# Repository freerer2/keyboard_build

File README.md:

## Note
빌드 한 키보드의 부품 정보 모음.
내 손길이 조금이라도 닿은 경우에만 목록에 추가됨.

## Keyboard List
- [blackpill_chayribdis_nano](/blackpill_chayribdis_nano/) : chayribdis_nano 블랙필버전(케이스 수정)
- [cantor-remix_MX](https://github.com/freerer2/cantor-remix_MX) : cantor-remix MX버전(PCB수정)
- [lazyboy36](/lazyboy36/) : 36키 모노블럭 키보드(ergogen 사용)

## unused
- ~~[wireless_charybdis_nano](/wireless_charybdis_nano/) : chayribdis_nano 무선버전(작성중)~~

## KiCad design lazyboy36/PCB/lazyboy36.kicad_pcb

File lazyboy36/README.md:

# LAZYBOY36
<center></center>
<center></center>

스플릿 키보드는 휴대시 trrs 케이블, USB 케이블, 오른쪽 키보드, 왼쪽 키보드  
아주 주렁주렁 정신이 없습니다.

이제는 USB 케이블과 키보드 한개만 챙기세요. Lazyboy36 입니다.

## Features

1. 당신의 손가락 건강을 위한 컬럼스태거 구조
2. 당신의 손목 건강을 위한 36키
3. 당신의 어깨 건강을 위한 20도 각도의 스플릿 구조
4. 당신의 타건감 취향을 위한 핫스왑 지원
5. 빌드의 범용성을 위한 Pro Micro 모양의 MCU 지원
6. 배터리 걱정할 필요없는 ONLY 유선키보드
7. 그 유명한 Miryoku 배열의 키맵을 한국인의 손에 맞춘 개조판 펌웨어 기본 지원
   - [lazybones](https://github.com/freerer2/qmk_firmware/tree/master/users/lazybones)
8. ~~휴대성이 좋은 아주 얇은 키보드~~(증명필요)
   - ~~키캡 없이 범폰 포함 총 높이 : 약 14mm~~
   - ~~케이스 높이 : 5.2mm~~

## Quick Links

- Ergogen Config: [config.yaml](config.yaml)
  - Ergogen command
  ```bash
  ergogen . && for i in output/cases/*.jscad; do npx @jscad/cli@1 "$i" -of stla; done
  ```
- PCB Design: [output/pcbs/lazyboy36.kicad_pcb](output/pcbs/lazyboy36.kicad_pcb)
- 3D Printable case: [output/cases/case.stl](output/cases/case.stl)
- QMK Config: [qmk_config/](qmk_config/)

## Bill of Materials (BOM)

### Keyboard

| Part name                         | Amount | Link                                                                   | note          |
| :-------------------------------- | -----: | :--------------------------------------------------------------------- | :------------ |
| PCB                               |      1 | [/lazyboy36/output/pcbs/gerber.zip](/lazyboy36/output/pcbs/gerber.zip) | JLC 주문완료  |
| MCU(such as the Pro Micro)        |      1 |                                                                        | 알리 주문완료 |
| Pin headers(optional)             |     24 |                                                                        | 알리 주문완료 |
| OLED(optional)                    |      1 |                                                                        |
| Choc v1 switchs(PG1350)           |     36 | https://ko.aliexpress.com/item/1005005883472162.html                   | 알리 주문완료 |
| Choc v1 keycaps                   |     36 | https://github.com/freerer2/choc_keycaps                               | JLC 주문완료  |
| 1N4148 SOD123 or DO-35            |     36 | https://ko.aliexpress.com/item/1005002882901030.html                   | 있음          |
| Kailh low profile hot-swap socket |     36 | https://ko.aliexpress.com/item/1005006345544915.html                   | 알리 주문완료 |
| Button, 4x4x1.5                   |      1 | https://ko.aliexpress.com/item/1005003918757433.html                   | 있음          |

### Case

| Part name                     | Amount | Link                                                                 | note          |
| :---------------------------- | -----: | :------------------------------------------------------------------- | :------------ |
| Case                          |      1 | [/lazyboy36/output/cases/case.stl](/lazyboy36/output/cases/case.stl) | JLC 주문완료  |
| Black 10x2mm bumpon           |      8 | https://ko.aliexpress.com/item/1005005287385986.html                 | 있음          |
| Screws, M2 3mm                |      8 | https://smartstore.naver.com/boltmall/products/106695149             | 알리 주문완료 |
| Heated screw insert, M2x2x3.2 |      8 | https://ko.aliexpress.com/item/1005004870993068.html                 | 알리 주문완료 |

# TODO-LIST

## ERGOGEN

- [x] 키보드 정의

## PCB

- [x] 라우팅

## FIRMWARE

- [x] QMK
- [ ] ~~VIA~~(고민중)

## BUILD

- [x] 재료준비
  - [x] PCB
    - [x] MCU : RP2040 PROMICRO
    - [x] SWITCH : PG1350
    - [x] KEYCAPS : MBK
    - [x] DIODE : SOD123
    - [x] HEADER PIN FEMALE : 315-43-112-41-003000
    - [x] HEADER PIN MALE : 3320-0-00-15-00-00-03-0
    - [x] HOTSWAP SOCKET
    - [x] RST BUTTON
  - [ ] CASE
    - [x] INSERT
    - [x] SCREWS
    - [x] BUMPON

## ETC

- [ ] README 작성
  - [x] Introduction
  - [x] Features
  - [x] Quick Links
    - [x] ergogen config yaml
    - [x] PCB
    - [x] CASE
    - [x] Firmware
      - [x] QMK
      - [ ] ~~VIA~~(고민중)
  - [x] BOM

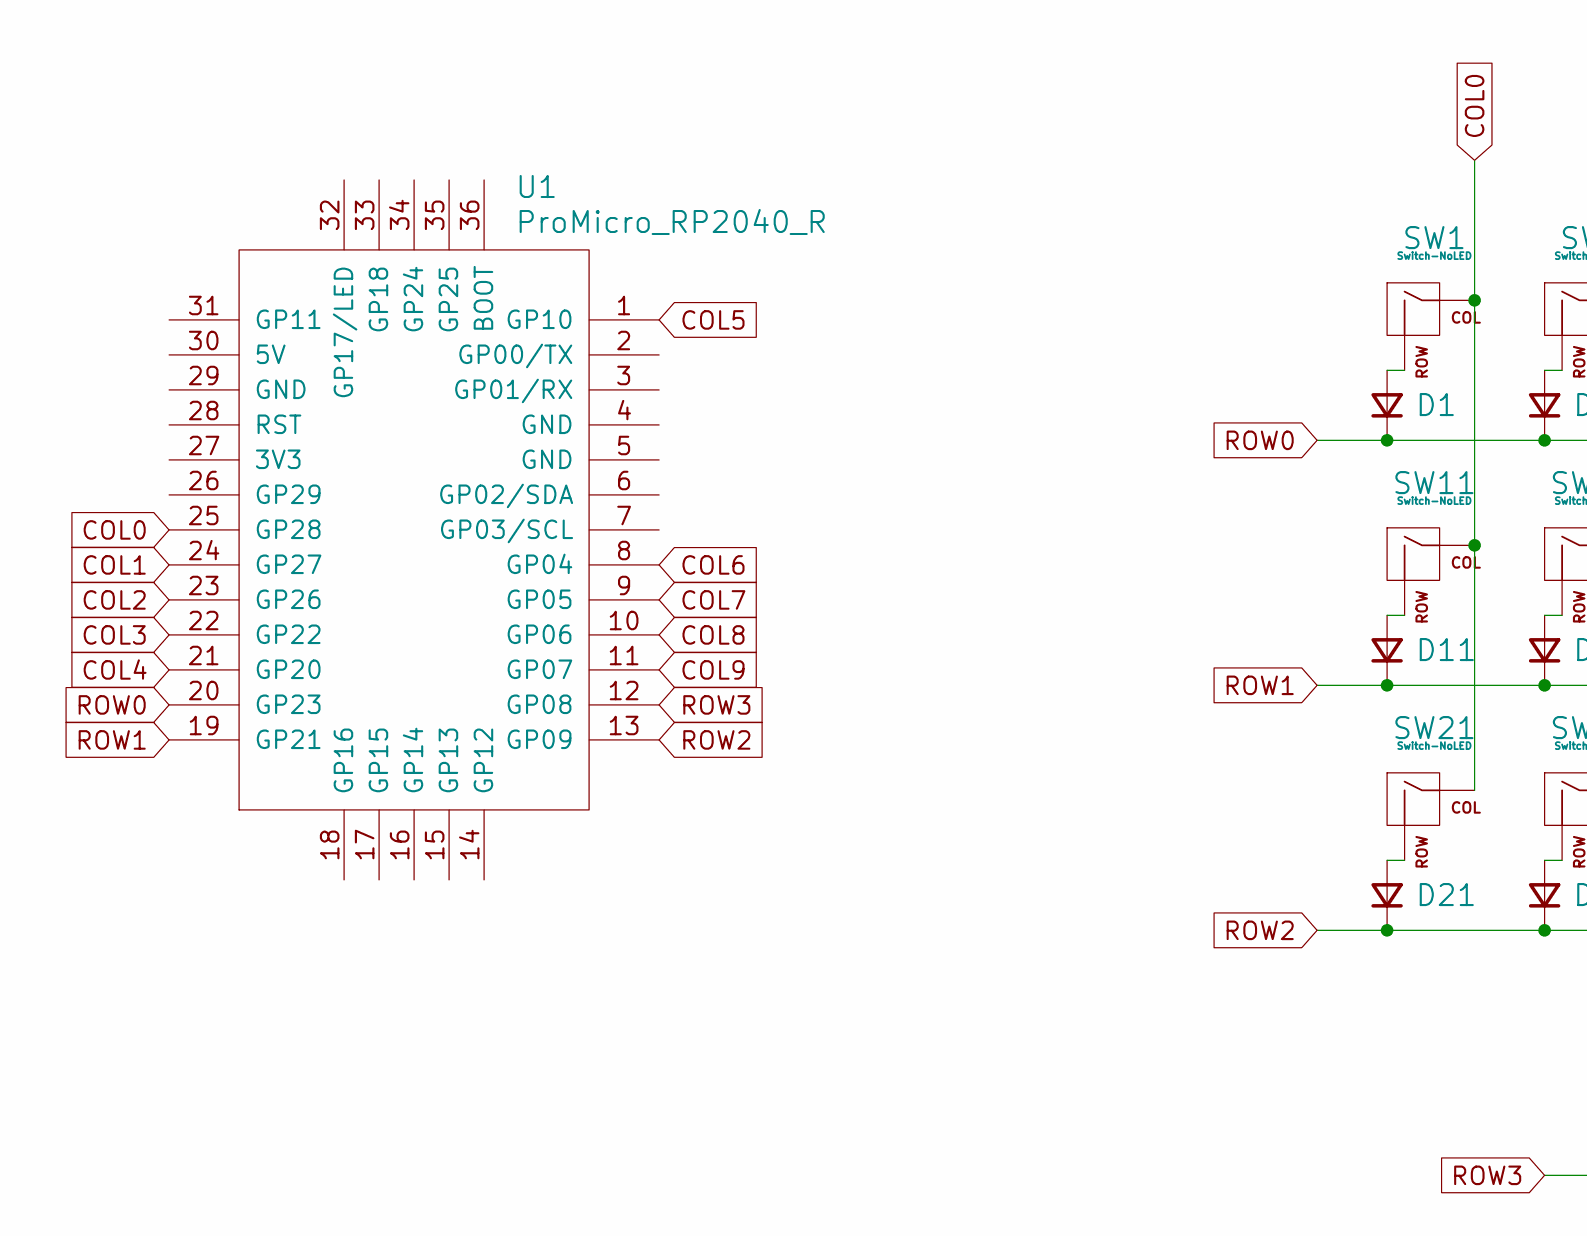
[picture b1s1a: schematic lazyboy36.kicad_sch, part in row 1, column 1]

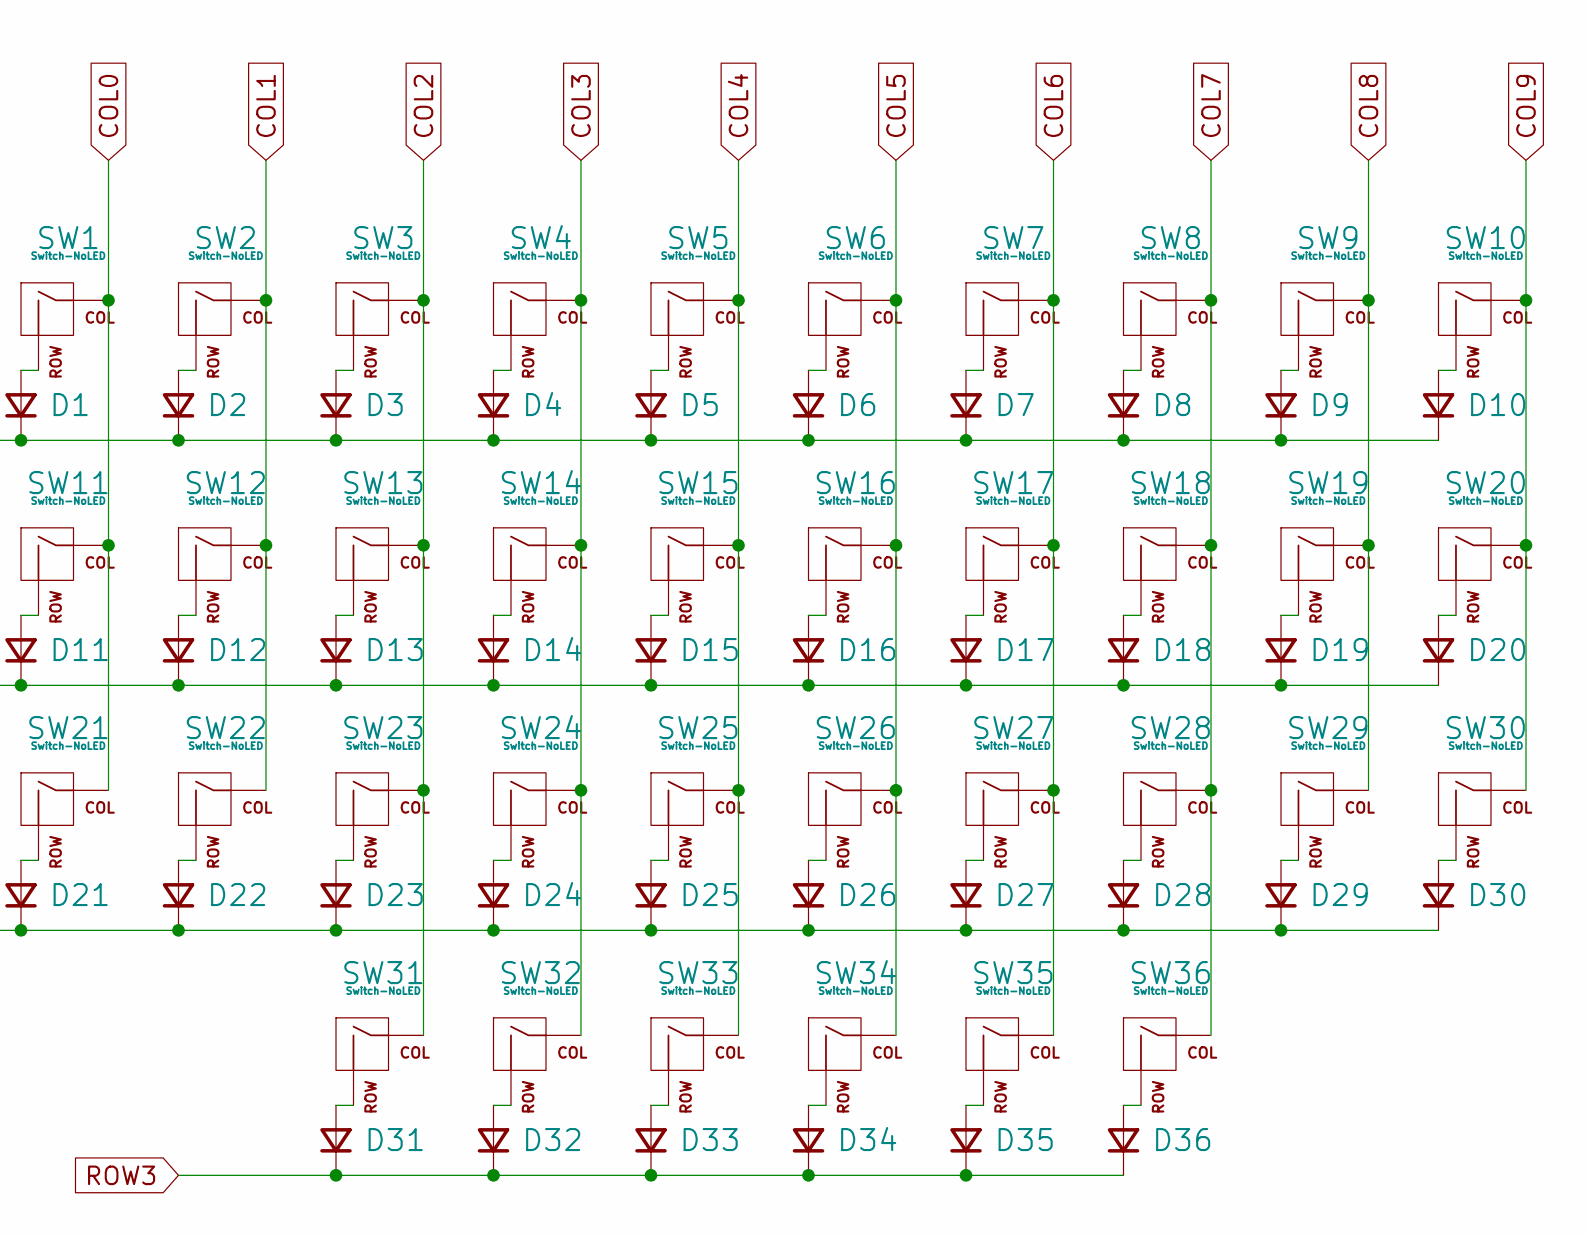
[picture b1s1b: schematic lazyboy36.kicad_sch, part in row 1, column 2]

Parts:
D1, D2, D3, D4, D5, D6, D7, D8, D9, D10, D11, D12, D13, D14, D15, D16, D17, D18, D19, D20, D21, D22, D23, D24, D25, D26, D27, D28, D29, D30, D31, D32, D33, D34, D35, D36: Diode; D3_TH_SMD_v2
SW1, SW2, SW3, SW4, SW5, SW6, SW7, SW8, SW9, SW10, SW11, SW12, SW13, SW14, SW15, SW16, SW17, SW18, SW19, SW20, SW21, SW22, SW23, SW24, SW25, SW26, SW27, SW28, SW29, SW30, SW31, SW32, SW33, SW34, SW35, SW36: Switch-NoLED; SW_Gateron_LowProfile_HotSwap_PTH
U1: ProMicro_RP2040_R; ProMicro_RP2040_v3.5_R

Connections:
COL0: SW1.1 (COL), SW11.1 (COL), SW21.1 (COL), U1.25 (GP28)
COL1: SW2.1 (COL), SW12.1 (COL), SW22.1 (COL), U1.24 (GP27)
COL2: SW3.1 (COL), SW13.1 (COL), SW23.1 (COL), SW31.1 (COL), U1.23 (GP26)
COL3: SW4.1 (COL), SW14.1 (COL), SW24.1 (COL), SW32.1 (COL), U1.22 (GP22)
COL4: SW5.1 (COL), SW15.1 (COL), SW25.1 (COL), SW33.1 (COL), U1.21 (GP20)
COL5: SW6.1 (COL), SW16.1 (COL), SW26.1 (COL), SW34.1 (COL), U1.1 (GP10)
COL6: SW7.1 (COL), SW17.1 (COL), SW27.1 (COL), SW35.1 (COL), U1.8 (GP04)
COL7: SW8.1 (COL), SW18.1 (COL), SW28.1 (COL), SW36.1 (COL), U1.9 (GP05)
COL8: SW9.1 (COL), SW19.1 (COL), SW29.1 (COL), U1.10 (GP06)
COL9: SW10.1 (COL), SW20.1 (COL), SW30.1 (COL), U1.11 (GP07)
unnamed: D1.2 (A), SW1.2 (ROW)
unnamed: D2.2 (A), SW2.2 (ROW)
unnamed: D3.2 (A), SW3.2 (ROW)
unnamed: D4.2 (A), SW4.2 (ROW)
unnamed: D5.2 (A), SW5.2 (ROW)
unnamed: D6.2 (A), SW6.2 (ROW)
unnamed: D7.2 (A), SW7.2 (ROW)
unnamed: D8.2 (A), SW8.2 (ROW)
unnamed: D9.2 (A), SW9.2 (ROW)
unnamed: D10.2 (A), SW10.2 (ROW)
unnamed: D11.2 (A), SW11.2 (ROW)
unnamed: D12.2 (A), SW12.2 (ROW)
unnamed: D13.2 (A), SW13.2 (ROW)
unnamed: D14.2 (A), SW14.2 (ROW)
unnamed: D15.2 (A), SW15.2 (ROW)
unnamed: D16.2 (A), SW16.2 (ROW)
unnamed: D17.2 (A), SW17.2 (ROW)
unnamed: D18.2 (A), SW18.2 (ROW)
unnamed: D19.2 (A), SW19.2 (ROW)
unnamed: D20.2 (A), SW20.2 (ROW)
unnamed: D21.2 (A), SW21.2 (ROW)
unnamed: D22.2 (A), SW22.2 (ROW)
unnamed: D23.2 (A), SW23.2 (ROW)
unnamed: D24.2 (A), SW24.2 (ROW)
unnamed: D25.2 (A), SW25.2 (ROW)
unnamed: D26.2 (A), SW26.2 (ROW)
unnamed: D27.2 (A), SW27.2 (ROW)
unnamed: D28.2 (A), SW28.2 (ROW)
unnamed: D29.2 (A), SW29.2 (ROW)
unnamed: D30.2 (A), SW30.2 (ROW)
unnamed: D31.2 (A), SW31.2 (ROW)
unnamed: D32.2 (A), SW32.2 (ROW)
unnamed: D33.2 (A), SW33.2 (ROW)
unnamed: D34.2 (A), SW34.2 (ROW)
unnamed: D35.2 (A), SW35.2 (ROW)
unnamed: D36.2 (A), SW36.2 (ROW)
ROW0: D1.1 (K), D2.1 (K), D3.1 (K), D4.1 (K), D5.1 (K), D6.1 (K), D7.1 (K), D8.1 (K), D9.1 (K), D10.1 (K), U1.20 (GP23)
ROW1: D11.1 (K), D12.1 (K), D13.1 (K), D14.1 (K), D15.1 (K), D16.1 (K), D17.1 (K), D18.1 (K), D19.1 (K), D20.1 (K), U1.19 (GP21)
ROW2: D21.1 (K), D22.1 (K), D23.1 (K), D24.1 (K), D25.1 (K), D26.1 (K), D27.1 (K), D28.1 (K), D29.1 (K), D30.1 (K), U1.13 (GP09)
ROW3: D31.1 (K), D32.1 (K), D33.1 (K), D34.1 (K), D35.1 (K), D36.1 (K), U1.12 (GP08)

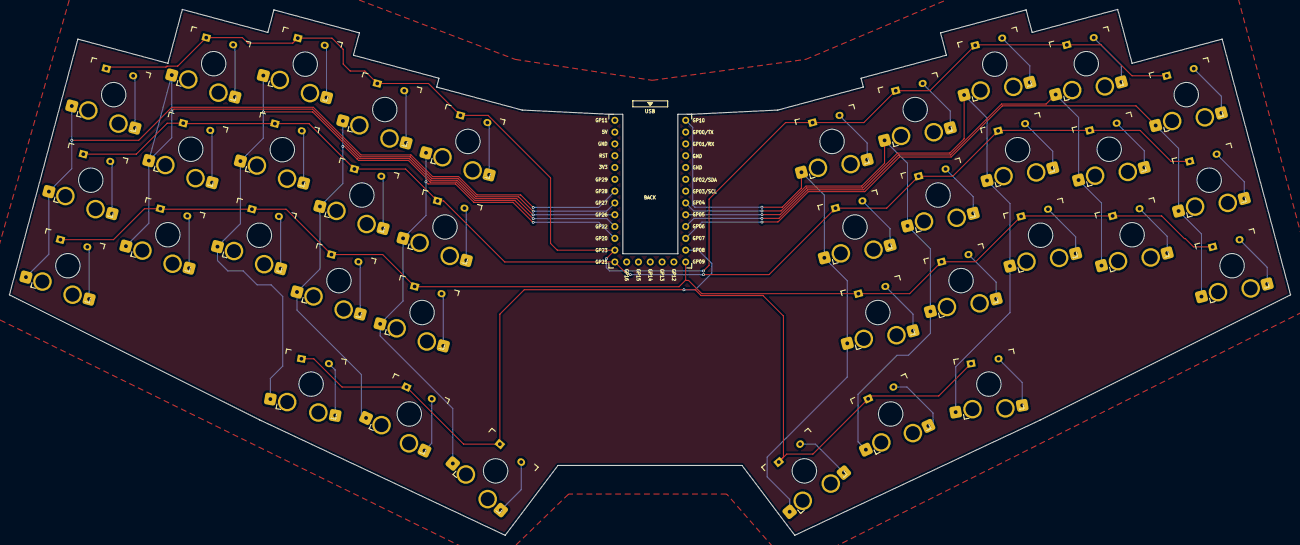
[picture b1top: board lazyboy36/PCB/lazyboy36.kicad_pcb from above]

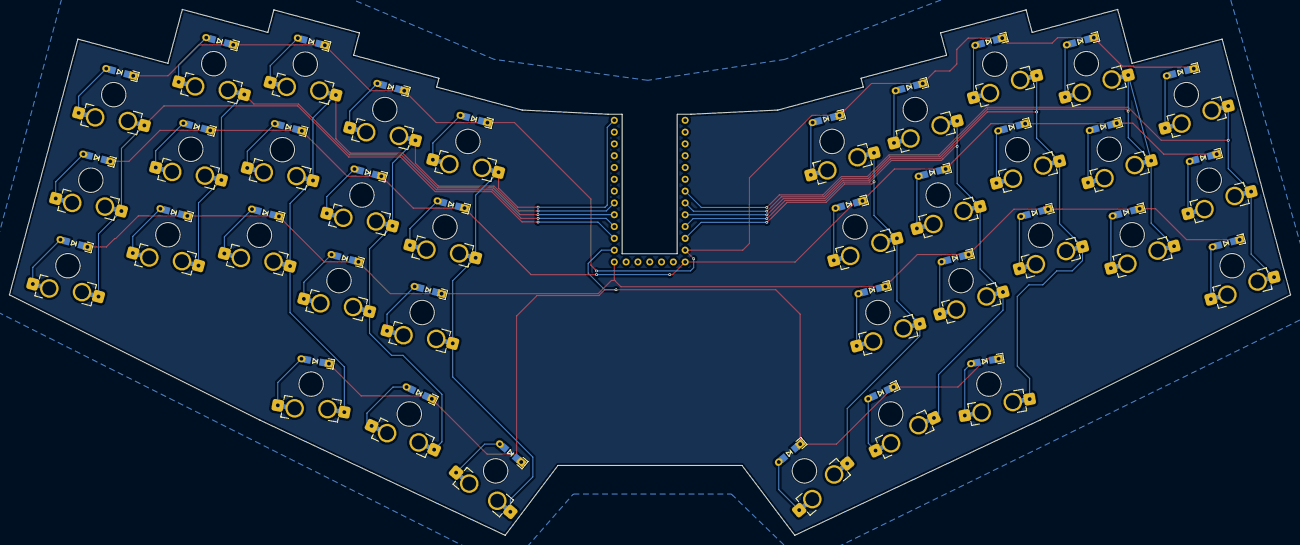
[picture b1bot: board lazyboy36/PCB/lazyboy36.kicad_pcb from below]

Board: 2 copper layers, 275.6 x 113.1 mm, 73 parts (36 on the bottom side), 50 nets.

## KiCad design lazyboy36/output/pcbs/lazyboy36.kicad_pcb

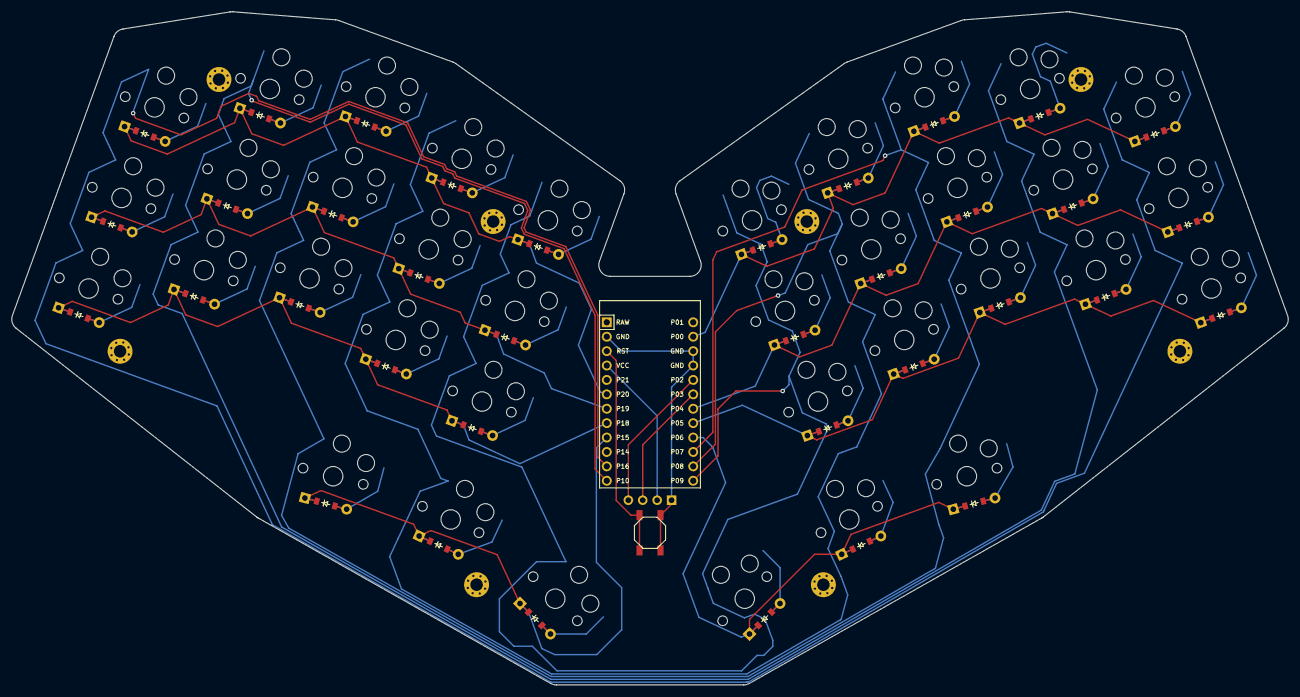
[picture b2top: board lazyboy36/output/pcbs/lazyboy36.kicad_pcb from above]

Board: 2 copper layers, 225.1 x 118.7 mm, 83 parts (0 on the bottom side), 54 nets.

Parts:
B1: SW_TACT_ALPS_SKQGABE010
D1, D2, D3, D4, D5, D6, D7, D8, D9, D10, D11, D12, D13, D14, D15, D16, D17, D18, D19, D20, D21, D22, D23, D24, D25, D26, D27, D28, D29, D30, D31, D32, D33, D34, D35, D36: ComboDiode
MCU1: ProMicro
OLED1: OLED; OLED_headers
S1, S2, S3, S4, S5, S6, S7, S8, S9, S10, S11, S12, S13, S14, S15, S16, S17, S18, S19, S20, S21, S22, S23, S24, S25, S26, S27, S28, S29, S30, S31, S32, S33, S34, S35, S36: PG1350
_1, _2, _3, _4, _5, _6, _7, _8: MountingHole_2.2mm_M2_Pad_Via

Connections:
GND: B1.1, MCU1.2, MCU1.15, MCU1.16, OLED1.1
P0: D21.1, D24.1, D27.1, D30.1, D33.1, MCU1.14
P2: MCU1.17, OLED1.4
P3: MCU1.18, OLED1.3
P4: D20.1, D23.1, D26.1, D29.1, D32.1, MCU1.19
P5: D19.1, D22.1, D25.1, D28.1, D31.1, MCU1.20
P6: D34.1, D35.1, D36.1, MCU1.21
P7: MCU1.22, S7.1, S8.1, S9.1, S16.1, S25.1, S26.1, S27.1, S34.1
P8: MCU1.23, S10.1, S11.1, S12.1, S17.1, S28.1, S29.1, S30.1, S35.1
P9: MCU1.24, S13.1, S14.1, S15.1, S18.1, S31.1, S32.1, S33.1, S36.1
P10: MCU1.12, S4.1, S5.1, S6.1, S22.1, S23.1, S24.1
P15: D16.1, D17.1, D18.1, MCU1.9
P16: MCU1.11, S1.1, S2.1, S3.1, S19.1, S20.1, S21.1
P18: D1.1, D4.1, D7.1, D10.1, D13.1, MCU1.8
P19: D2.1, D5.1, D8.1, D11.1, D14.1, MCU1.7
P20: D3.1, D6.1, D9.1, D12.1, D15.1, MCU1.6
RST: B1.2, MCU1.3
VCC: MCU1.4, OLED1.2
index_bottom: D10.2, S10.2
index_home: D11.2, S11.2
index_top: D12.2, S12.2
inner_bottom: D13.2, S13.2
inner_cluster: D18.2, S18.2
inner_home: D14.2, S14.2
inner_top: D15.2, S15.2
middle_bottom: D7.2, S7.2
middle_cluster: D17.2, S17.2
middle_home: D8.2, S8.2
middle_top: D9.2, S9.2
mirror_index_bottom: D28.2, S28.2
mirror_index_home: D29.2, S29.2
mirror_index_top: D30.2, S30.2
mirror_inner_bottom: D31.2, S31.2
mirror_inner_cluster: D36.2, S36.2
mirror_inner_home: D32.2, S32.2
mirror_inner_top: D33.2, S33.2
mirror_middle_bottom: D25.2, S25.2
mirror_middle_cluster: D35.2, S35.2
mirror_middle_home: D26.2, S26.2
mirror_middle_top: D27.2, S27.2
mirror_outer_cluster: D34.2, S34.2
mirror_pinky_bottom: D19.2, S19.2
mirror_pinky_home: D20.2, S20.2
mirror_pinky_top: D21.2, S21.2
mirror_ring_bottom: D22.2, S22.2
mirror_ring_home: D23.2, S23.2
mirror_ring_top: D24.2, S24.2
outer_cluster: D16.2, S16.2
pinky_bottom: D1.2, S1.2
pinky_home: D2.2, S2.2
pinky_top: D3.2, S3.2
ring_bottom: D4.2, S4.2
ring_home: D5.2, S5.2
ring_top: D6.2, S6.2

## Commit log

2023-11-01 init
2023-11-01 Update readme.md
    add bumpon
2024-01-09 업데이트
2024-01-29 wireless model update
2024-03-28 update md
2024-03-28 readme 파일명 작업1(대문자로 전환)
2024-03-28 readme 파일명 작업2(대문자로 전환)
2024-03-28 readme 파일명 작업3(대문자로 전환)
2024-03-28 readme 파일명 작업4(대문자로 전환)
2024-03-28 readme 파일명 작업5(대문자로 전환)
2024-03-28 README 업데이트
2024-03-28 다음부터 열심히 씀 ㄹㅇ 진짜로
2024-03-28 프로젝트 초기화
2024-03-28 심볼, 풋프린트 추가
2024-03-29 TODOLIST UPDATE
2024-03-29 TODOLIST 수정
2024-03-31 설계 중간 업로드
2024-03-31 중간 설계
2024-03-31 설계 진행
2024-03-31 소개 글 수정
2024-04-01 임시파일 삭제
2024-04-01 fsdf
2024-04-02 설계 거의 완료
2024-04-02 note 부품정보 추가
2024-04-03 설계변경, 불필요 배선 삭제
2024-04-03 설계 중단
2024-04-12 ergogen 설계
2024-04-12 케이스 높이 조절
2024-04-13 범폰 추가, 높이 1미리 상승
2024-04-13 키보드명 변경
2024-04-13 마운팅홀 위치 변경
2024-04-13 키보드 명 변경
2024-04-14 폴더 이동, 케이스 높이 1 낮춤
2024-04-14 높이수정
2024-04-14 소개글 변경
2024-04-14 README.md 업데이트
2024-04-15 빌드 진행상황 추가
2024-04-15 설명추가
2024-04-16 카리브리스 무선 미사용
2024-04-16 칸터 MX버전 분리
2024-04-16 설명 수정
2024-04-16 투두리스트 추가
2024-05-05 bom update
2024-05-06 케이스 높이 수정
2024-05-07 주문상태변경
2024-05-20 키보드 케이스 변경
2024-05-20 상태변경
2024-06-17 update 이미지
2024-06-17 qmk설정 추가
